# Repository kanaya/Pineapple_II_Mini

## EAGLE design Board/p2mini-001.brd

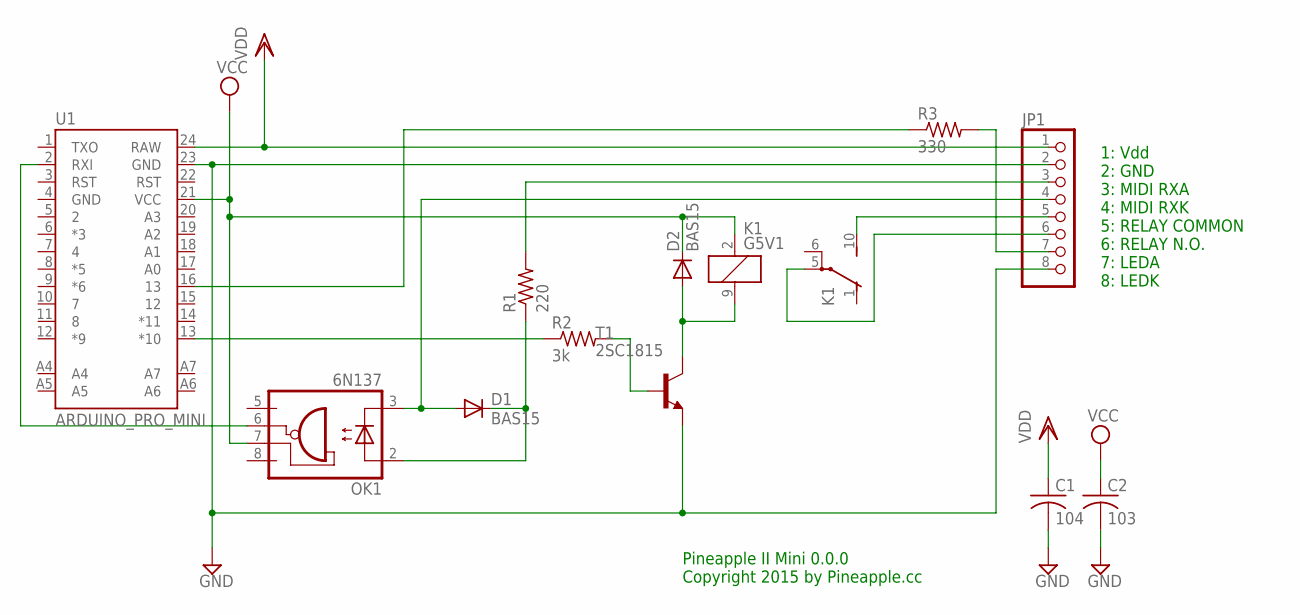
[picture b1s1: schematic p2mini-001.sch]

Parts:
C1: 104; C025-025X050
C2: 103; C025-025X050
D1, D2: BAS15; DO34-7
JP1: PINHD-1X8; 1X08
K1: G5V1
OK1: 6N137; DIL08
R1: 220; 0204/5
R2: 3k; 0204/5
R3: 330; 0204/5
T1: 2SC1815; TO92-ECB
U1: ARDUINO_PRO_MINI

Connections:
GND: C1.2, C2.2, JP1.2, JP1.8, T1.E, U1.23 (GND)
MIDI0: JP1.3, R1.2
MIDI1: D1.A, JP1.4, OK1.3 (C)
unnamed: JP1.5, K1.10 (S)
unnamed: D2.A, K1.9 (2), T1.C
unnamed: R2.1, U1.13 (*10)
unnamed: R2.2, T1.B
unnamed: JP1.6, K1.5
unnamed: R3.1, U1.16 (13)
unnamed: JP1.7, R3.2
unnamed: D1.C, OK1.2 (A), R1.1
RX: OK1.6 (VO), U1.2 (RXI)
VCC: C2.1, D2.C, K1.2 (1), OK1.7 (VE), U1.21 (VCC)
VDD: C1.1, JP1.1, U1.24 (RAW)

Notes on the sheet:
Pineapple II Mini 0.0.0 Copyright 2015 by Pineapple.cc
1: Vdd 2: GND 3: MIDI RXA 4: MIDI RXK 5: RELAY COMMON 6: RELAY N.O. 7: LEDA 8: LEDK

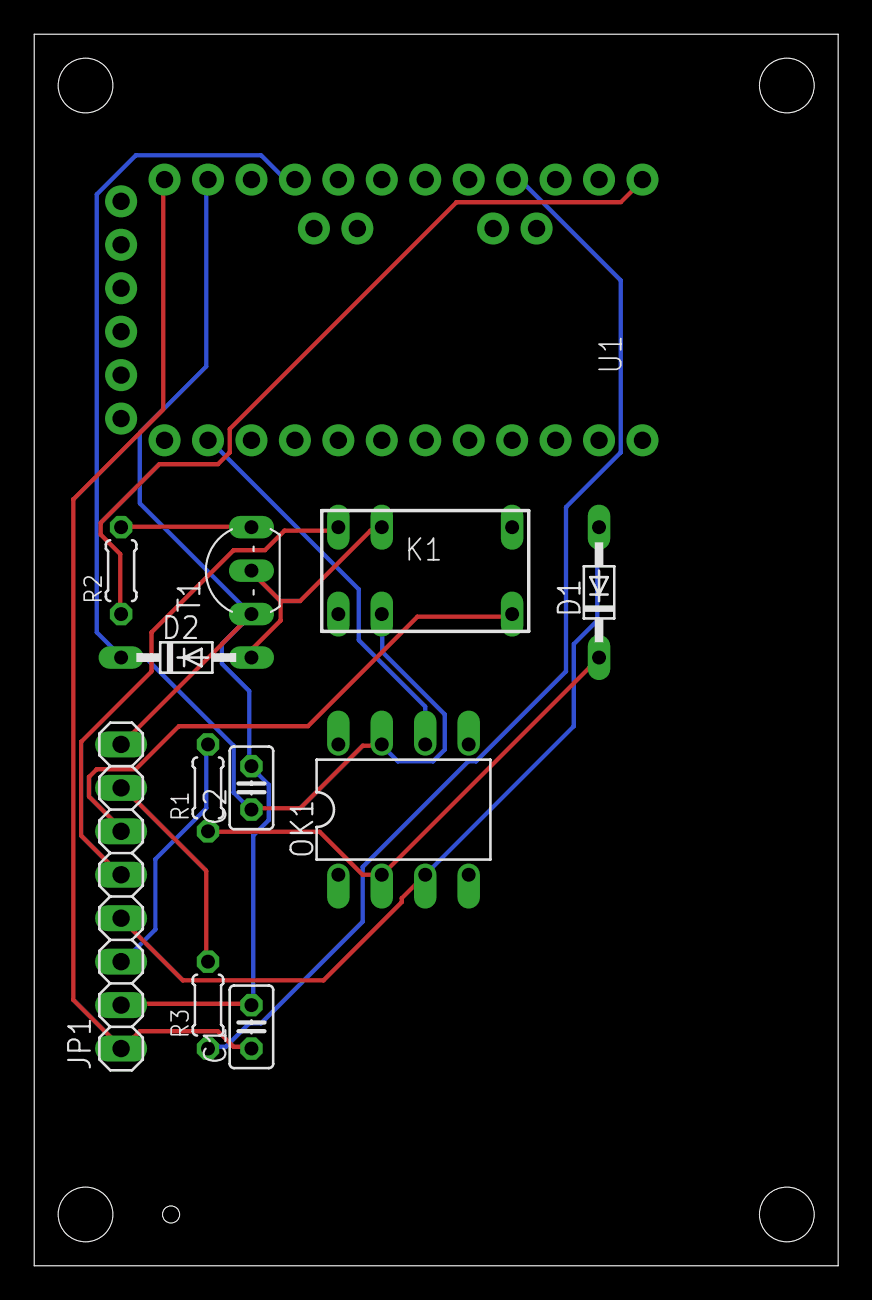
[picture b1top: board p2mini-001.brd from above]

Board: 2 copper layers, 47.0 x 72.0 mm, 12 parts (0 on the bottom side), 14 nets.

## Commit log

2015-02-11 first design.
2015-02-11 Added parts.md
2015-02-11 Added some parts.
2015-02-13 release

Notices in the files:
parts and their libraries:
SparkFun-Boards: Licensing: Creative Commons ShareAlike 4.0 International - https://creativecommons.org/licenses/by-sa/4.0
